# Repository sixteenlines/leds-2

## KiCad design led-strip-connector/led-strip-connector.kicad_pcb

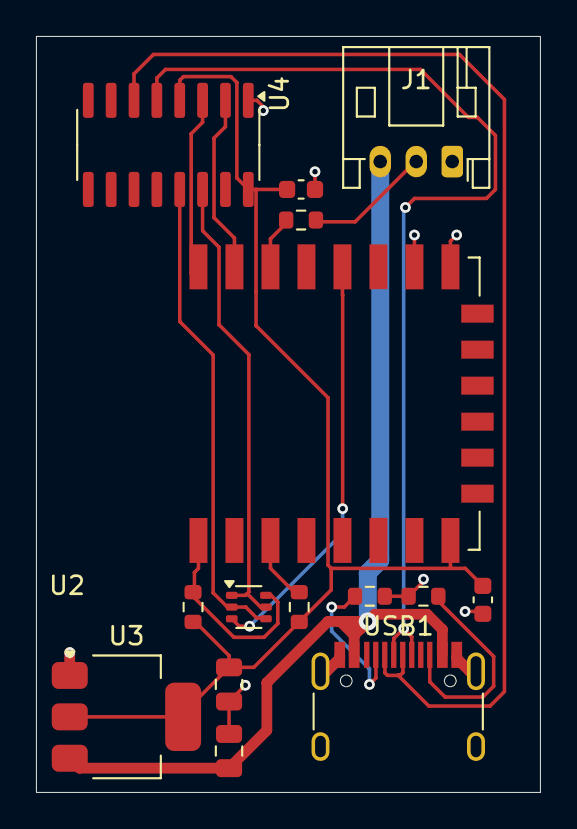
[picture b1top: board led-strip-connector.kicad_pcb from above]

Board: 2 copper layers, 28.0 x 42.0 mm, 15 parts (0 on the bottom side), 16 nets.

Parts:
C1, C2: 100n; C_0603_1608Metric
C3, C4: 2.2u; C_0805_2012Metric
J1: Conn_01x03_Pin; JST_PH_S3B-PH-K_1x03_P2.00mm_Horizontal
Q1: UMH3N; SOT-363_SC-70-6
R1: 330; R_0603_1608Metric
R2, R3: 10K; R_0603_1608Metric
R4, R5: 5K1; R_0603_1608Metric
U2: ESP-12F; ESP-12E
U3: LM1117MP-3.3; SOT-223-3_TabPin2
U4: CH340C; SOIC-16_3.9x9.9mm_P1.27mm
USB1: USB4105-GF-A; USB_C_Receptacle_HRO_TYPE-C-31-M-12

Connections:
+3V3: C1.1, C2.2, C4.1, R2.2, R3.1, U2.8 (VCC), U3.2 (VO), U4.4 (V3), U4.16 (VCC)
+5V: C3.1, J1.3, U3.3 (VI), USB1.A4 (VBUS), USB1.A9 (VBUS), USB1.B4 (VBUS), USB1.B9 (VBUS)
DTR: Q1.2 (B1), Q1.4 (E2), U4.13 (~DTR)
GND: C1.2, C2.1, C3.2, C4.2, J1.1, R4.2, R5.2, U2.15 (GND), U2.16 (GPIO15), U3.1 (GND), U4.1 (GND), USB1.A1 (GND), USB1.A12 (GND), USB1.B1 (GND), USB1.B12 (GND), USB1.S1 (SHIELD)
unnamed: J1.2, R1.2
unnamed: Q1.6 (C1), R3.2, U2.1 (~RST)
unnamed: Q1.3 (C2), U2.18 (GPIO0)
unnamed: R2.1, U2.3 (EN)
unnamed: R1.1, U2.20 (GPIO5)
unnamed: R5.1, USB1.A5 (CC1)
unnamed: R4.1, USB1.B5 (CC2)
RTS: Q1.1 (E1), Q1.5 (B2), U4.14 (~RTS)
RX: U2.21 (GPIO3/RXD), U4.2 (TXD)
TX: U2.22 (GPIO1/TXD), U4.3 (RXD)
USBD+: U4.5 (UD+), USB1.A6 (D+), USB1.B6 (D+)
USBD-: U4.6 (UD-), USB1.A7 (D-), USB1.B7 (D-)

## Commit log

2023-12-09 new improved version
2023-12-10 corrected num leds
2023-12-13 testing if restarting fixes idle issue
2023-12-14 added reset button
2024-05-19 added plant mode beta
2024-05-20 adjusted plant mode rgb values
2024-08-10 added kicad strip connector board
2024-08-21 new pcb
2024-09-13 maybe working sunset/sunrise detection
2024-09-14 actually working sunset/sunrise time
2024-09-14 fixed borked dst
